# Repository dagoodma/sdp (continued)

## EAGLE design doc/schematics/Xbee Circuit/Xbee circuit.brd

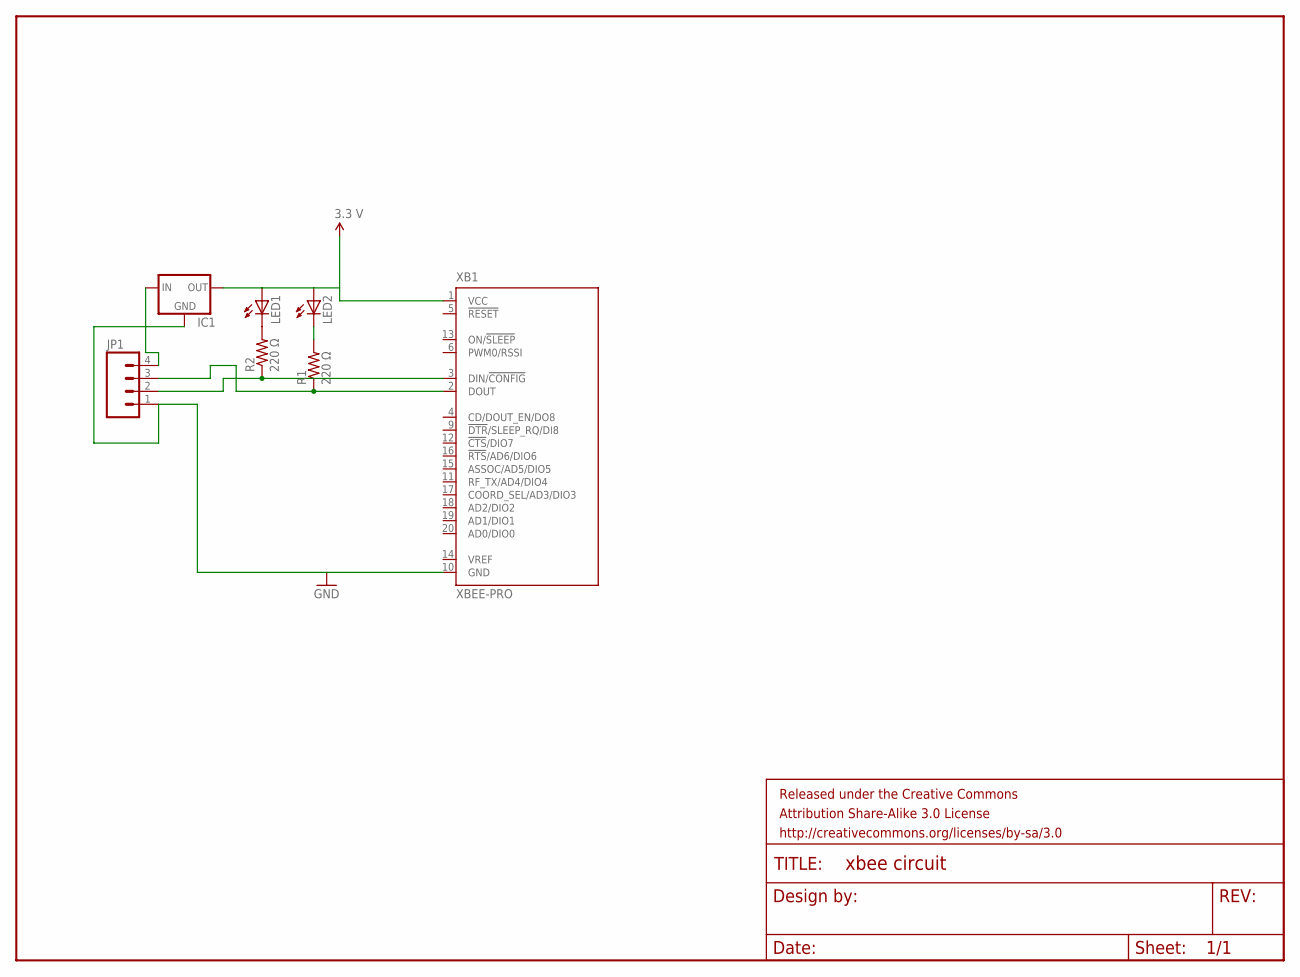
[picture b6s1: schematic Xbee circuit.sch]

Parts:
FRAME1: FRAME-LETTER; CREATIVE_COMMONS
IC1: V_REG_78XXSINK; TO220-IGO
JP1: M04LOCK; 1X04_LOCK
LED1, LED2: LED5MM
R1, R2: 220 Ω; AXIAL-0.4
XB1: XBEE-PRO

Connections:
GND: IC1.GND, JP1.1, XB1.10 (GND)
unnamed: LED2.K (C), R1.P$2 (2)
unnamed: LED1.K (C), R2.P$2 (2)
unnamed: JP1.2, R2.P$1 (1), XB1.3 (DIN/!CONFIG)
unnamed: JP1.3, R1.P$1 (1), XB1.2 (DOUT)
unnamed: IC1.IN, JP1.4
VCC: IC1.OUT, LED1.A, LED2.A, XB1.1 (VCC)

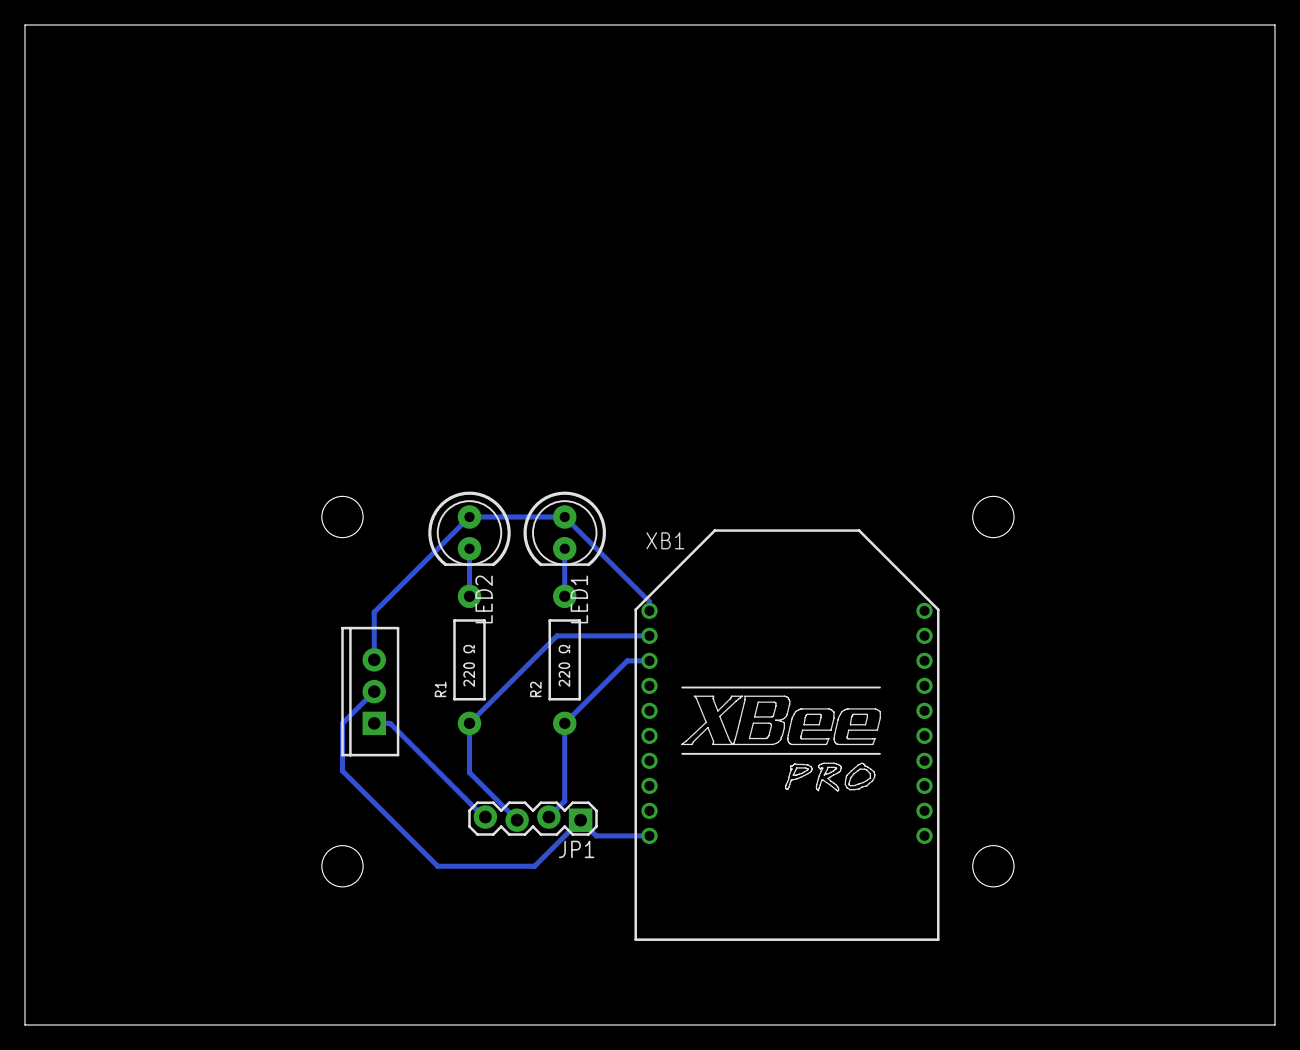
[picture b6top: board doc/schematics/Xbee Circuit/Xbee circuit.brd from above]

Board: 2 copper layers, 100.0 x 80.0 mm, 12 parts (0 on the bottom side), 7 nets.

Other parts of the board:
U$1, U$2, U$3, U$4: STAND-OFF

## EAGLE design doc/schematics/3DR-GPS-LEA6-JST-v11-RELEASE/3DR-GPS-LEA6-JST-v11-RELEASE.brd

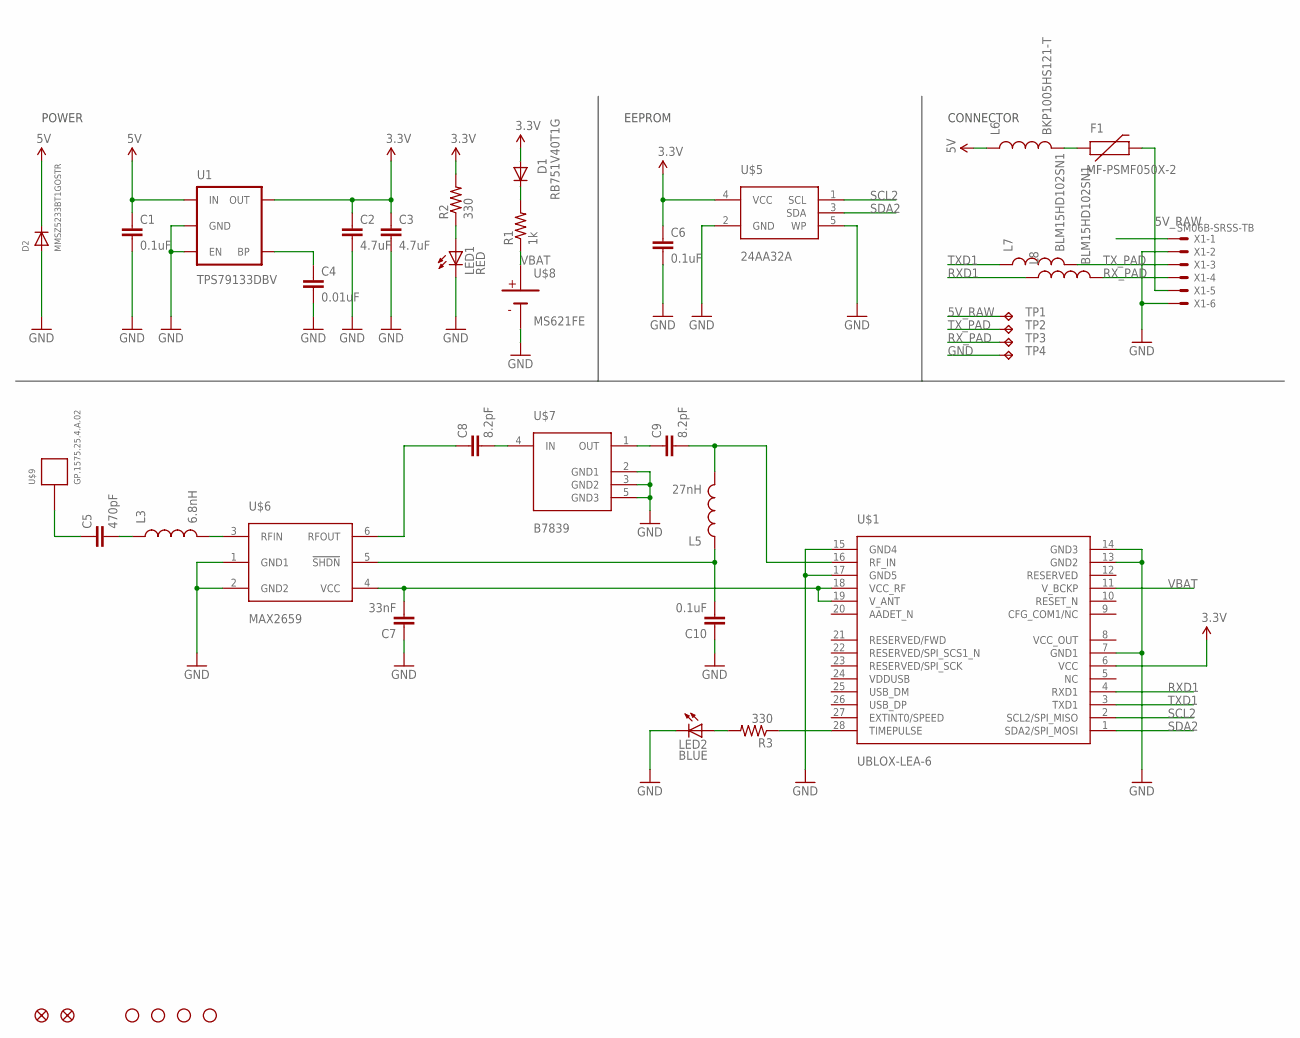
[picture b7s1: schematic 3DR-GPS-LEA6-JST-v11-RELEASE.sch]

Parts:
C1, C6, C10: 0.1uF; 0402-CAP
C2, C3: 4.7uF; 0805
C4: 0.01uF; 0402-CAP
C5: 470pF; 0402-CAP
C7: 33nF; 0402-CAP
C8, C9: 8.2pF; 0402-CAP
D1: RB751V40T1G; SOD-323
D2: MMSZ5233BT1GOSTR; SOD-123
F1: MF-PSMF050X-2; 0805
JP1, JP2: FIDUCIAL1X2; FIDUCIAL-1X2
JP3, JP4, JP5, JP6: STAND-OFF
L3: 6.8nH; C0402
L5: 27nH; C0402
L6: BKP1005HS121-T; 0402-IND
L7, L8: BLM15HD102SN1; 0402-IND
LED1: RED; LED-0603
LED2: BLUE; LED-0603
R1: 1k; 0402-RES
R2, R3: 330; 0402-RES
TP1, TP2, TP3, TP4: TPTP20SQ; TP20SQ
U1: TPS79133DBV; SOT23-5
U$1: UBLOX-LEA-6
U$5: 24AA32A; SOT23-5
U$6: MAX2659; UDFN-6
U$7: B7839; QCS5E
U$8: MS621FE
U$9: GP.1575.25.4.A.02
X1: SM06B-SRSS-TB

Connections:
3.3V: C2.1, C3.1, C6.1, D1.2 (A), R2.2, U1.5 (OUT), U$1.6 (VCC), U$5.4 (VCC)
5V: C1.1, D2.C, L6.1, U1.1 (IN)
5V_RAW: F1.2, TP1.TP, X1.5
GND: C1.2, C2.2, C3.2, C4.2, C6.2, C7.1, C10.1, D2.A, LED1.C, LED2.C, TP4.TP, U1.2 (GND), U1.3 (EN), U$1.7 (GND1), U$1.13 (GND2), U$1.14 (GND3), U$1.15 (GND4), U$1.17 (GND5), U$5.2 (GND), U$5.5 (WP), U$6.1 (GND1), U$6.2 (GND2), U$7.2 (GND1), U$7.3 (GND2), U$7.5 (GND3), U$8.2 (NEG), X1.2, X1.6
unnamed: L3.2, U$6.3 (RFIN)
unnamed: C4.1, U1.4 (BP)
unnamed: C5.2, L3.1
unnamed: C8.2, U$7.4 (IN)
unnamed: R3.1, U$1.28 (TIMEPULSE)
unnamed: C9.1, U$7.1 (OUT)
unnamed: C7.2, U$1.18 (VCC_RF), U$1.19 (V_ANT), U$6.4 (VCC)
unnamed: C8.1, U$6.6 (RFOUT)
unnamed: C10.2, L5.1, U$6.5 (!SHDN)
unnamed: C5.1, U$9.1
unnamed: C9.2, L5.2, U$1.16 (RF_IN)
unnamed: D1.1 (C), R1.2
unnamed: LED1.A, R2.1
unnamed: LED2.A, R3.2
unnamed: F1.1, L6.2
RXD1: L8.1, U$1.4 (RXD1)
RX_PAD: L8.2, TP3.TP, X1.4
SCL2: U$1.2 (SCL2/SPI_MISO), U$5.1 (SCL)
SDA2: U$1.1 (SDA2/SPI_MOSI), U$5.3 (SDA)
TXD1: L7.1, U$1.3 (TXD1)
TX_PAD: L7.2, TP2.TP, X1.3
VBAT: R1.1, U$1.11 (V_BCKP), U$8.1 (POS)

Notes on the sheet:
POWER
EEPROM
CONNECTOR

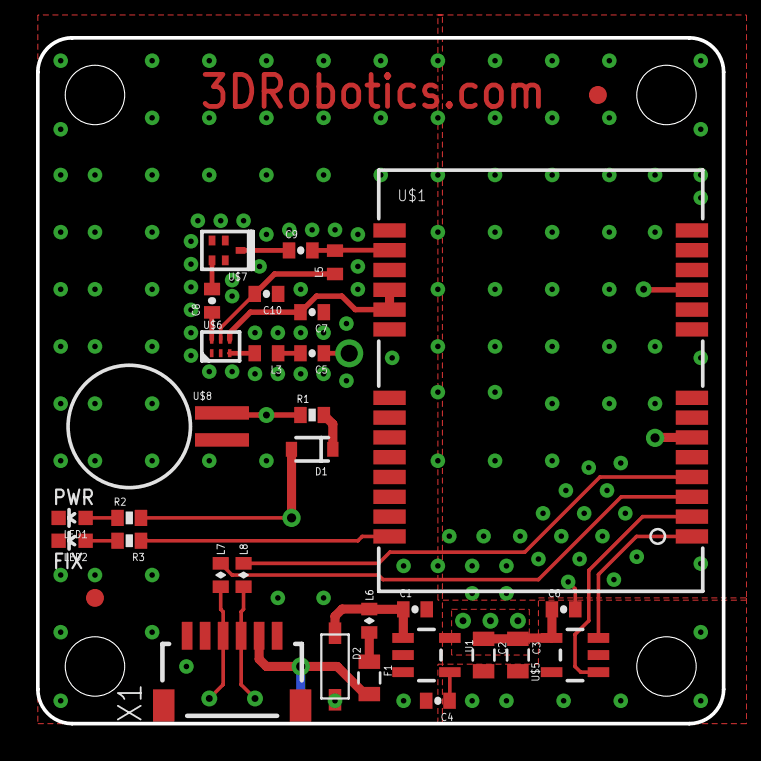
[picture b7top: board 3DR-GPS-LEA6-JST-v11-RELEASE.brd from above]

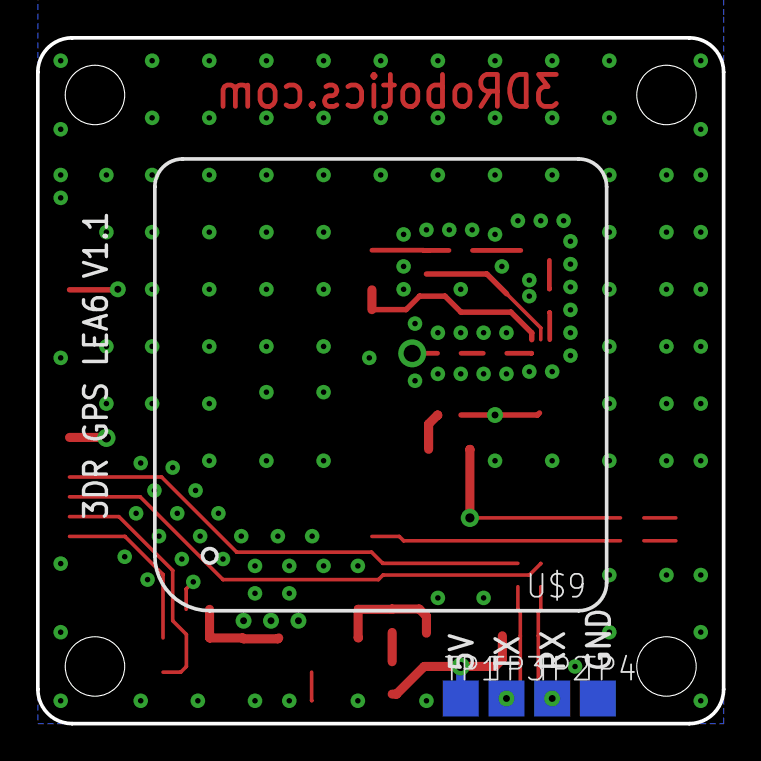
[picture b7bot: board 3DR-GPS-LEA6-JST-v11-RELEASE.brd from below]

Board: 4 copper layers, 38.1 x 38.1 mm, 41 parts (5 on the bottom side), 26 nets.

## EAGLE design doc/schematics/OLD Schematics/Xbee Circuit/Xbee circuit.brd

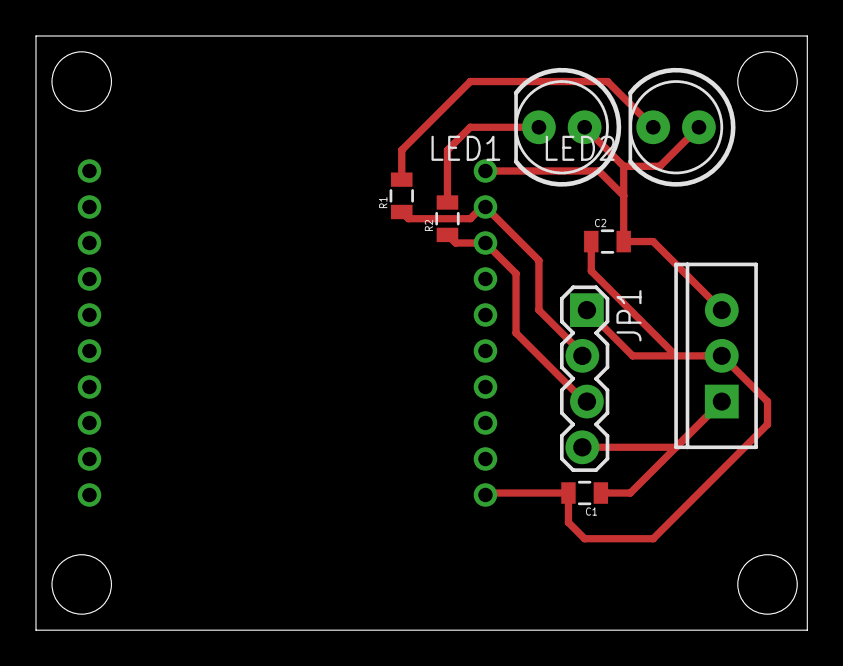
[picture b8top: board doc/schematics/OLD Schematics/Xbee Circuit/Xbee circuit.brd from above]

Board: 2 copper layers, 42.9 x 33.0 mm, 14 parts (1 on the bottom side), 7 nets.

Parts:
C1: 4.7 uF; 0805
C2: 1 uF; 0805
FRAME1: FRAME-LETTER; CREATIVE_COMMONS
IC1: TO220-IGO
JP1: 1X04_LOCK
LED1, LED2: LED5MM
R1, R2: 220 Ω; 0805
U$1, U$2, U$3, U$4: STAND-OFF
XB1: XBEE-PRO

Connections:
GND: C1.2, C2.1, IC1.GND, JP1.1, XB1.10
unnamed: LED2.K, R1.2
unnamed: LED1.K, R2.2
unnamed: JP1.3, R2.1, XB1.3
unnamed: JP1.2, R1.1, XB1.2
unnamed: C1.1, IC1.IN, JP1.4
VCC: C2.2, IC1.OUT, LED1.A, LED2.A, XB1.1

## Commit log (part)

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2012-12-28 Initial commit.
2012-12-28 Added README. Removed braindump.
2012-12-28 Quoted ascii in README.
2012-12-28 Added tool directory.
2012-12-28 Improved github readme.
2013-01-05 Added notes, refs, datasheets, examples folder, images, financial docs, and updated gps model functions.
2013-01-09 Added kresge app, blackwell paper, charter, notes...
2013-01-16 Added presentations.
2013-01-16 Added to Kresge funding proposal.
2013-01-17 Added Background to Kresge Doc
2013-01-17 Objectives section for Funding Proposal
2013-01-17 Added unfinished procedure section.
2013-01-17 Compiled kresge funding doc.
2013-01-17 Added another latex file to gitignore.
2013-01-17 Small change to kresge proposal, reorganized doc folder.
2013-01-17 Finalized kresge proposal cover sheet, budget, and letters of rec.
2013-01-17 Added newest kresge cover sheet.
2013-01-18 Added Kresge funding packet final.
2013-01-19 I2C module Header and C File. Implemented Start, Stop, Send Byte.
2013-01-19 Included the First iteration of the UART code. We still need to test the code and guarantee that it is working properly.
    I also deleted a file that I believe was causing errors. It was 0 bytes, and the folder said that it had been modified, when it had not.
2013-01-19 These are my initial Xbee Files. I believe these are all the files I will need.
    Now that Uart.c is started I can begin implementing the correct functions into the Xbee.c. There will be updated again in the next few days.
2013-01-22 Completed I2C library and Barometer.
2013-01-22 Added local makefile to ignore.
2013-01-23 Updated .gitignore to add temp directory.
2013-01-23 Removed repository files.
2013-01-23 Barometer changes, started accelerometer but not finished.
2013-01-24 Finishing UART and XBee modules.
2013-01-24 Merged Johns Xbee code.
2013-01-25 Reformatted itemized budget. Added thermal MATLAB code, and added data sheets.
2013-01-25 Updated documentation and added doxygen API.
2013-01-25 Added general proposal.
2013-01-29 Finished some of the GPS MATLAB model code. Ready for test.
2013-01-29 Added kml support to GPS model.
2013-01-29 Fixed matlab twos comp conversion issue. Saw correct long lat coordinates.
2013-01-30 Finished 2D scatter plot with stats. Ready for extensive GPS tests.
2013-02-02 Updated comments to code
2013-02-05 Added february newsletter.
2013-02-08 Added GPS code, updated doxygen, added gps data plots, modified Board and Serial modules.
2013-02-10 Updated GPS state machine.
2013-02-10 Thermal module and project added. Ready for MATLAB analysis.
2013-02-10 Merged David and Shahs Barometer code.
2013-02-10 Finished GPS lat,lon,alt code. Still need velocity and error setting.
2013-02-10 Encoders up on new base.
2013-02-10 Non-working encoder code!
2013-02-11 Encoder code that dumps angle value through serial. No running avg. implemented yet.
2013-02-11 Mavlink up and working
2013-02-13 Added serial logging tool and miniterm.
    Next comes py2exe and some fine tuning for serial_logger.
2013-02-13 Small fixes to Xbee Test and #defines
2013-02-14 Added serial logger. Has one error.
    Unexplainable error showing up in data character from serial.read(1):
    Error: Sent byte was not acknowledged
2013-02-14 Finished and merged serial_logger.
2013-02-14 Finished thermal MATLAB code.
2013-02-14 Improved GPS scirpts.
2013-02-14 GPS convergence test. Want mean squared sum now.
2013-02-14 Thermal,baro,and solidworks changes.
2013-02-14 Finished GPS convergence scripts.
2013-02-15 MATLAB code that outputs pixels in the appropriate orientation. Set up for 4Hz.
2013-02-15 Set Xbee Channel into program mode. Tried to make the Send and Recieve dest address working. I was unable to get it to work.
    I also setup XBEE_1 #defines
2013-02-16 Ready to add console window to gui.
2013-02-17 Set up Dest and Source addresses
2013-02-17 Finished gui, but one bug crashes.
2013-02-17 Possibly fixed crashing. Added file menus and removed locks.
2013-02-17 Sonar Compiling
2013-02-23 Finished gui and packed in exe for win.
    Need mac app, and need icon in tkinter.
2013-02-23 New GPS convergence data.
2013-02-23 Finished non-bundles serial_logger, and fixed gps record test to be more robust.
2013-02-23 Fixed gps record test to record timesteps.
2013-02-23 Fixed gps record test time stamps.
2013-02-23 Fixed timestamp recorded gps.
2013-02-23 Fixed timestamps in gps record and improved script.
2013-02-25 xbee Test and Xbee heart beat now working.
2013-02-25 Broken Sonar, about to create a new project.
2013-02-25 Sonar Compiling, and getting proper data. Analog window does not seem to be working.
2013-02-26 Added Mavlink message Start_rescue
2013-02-26 Initial creation of Compass project
2013-02-28 Accelerometer accum and indicator test. Improvements to logger speed.
2013-03-01 Added GPS error correction code to pic, and MATLAB test.
2013-03-07 Message added to Mavlink.c
2013-03-07 Renamed Sonar Project
2013-03-09 Encoders, barometer, Magnetometer, Position module.
2013-03-09 Added Ack, need to transfer over to Compass branch
2013-03-09 Started newletter, added accelerometer into CC.
2013-03-10 Xbee Ack Working
2013-03-10 Added ifdef to compas accelerometer.
2013-03-10 Proper placement of solidworks and schematics
2013-03-10 ACKs now in RUN_SM need to test this on another computer.
2013-03-10 Began work on ACKS
2013-03-10 Navigation library added. Encoder and COMPAS updated with GPS.
2013-03-10 Fixed GPS project, added Navigation, fixed COMPAS.
2013-03-14 Compas compiles with navgiation changes.
2013-03-14 Not compiling, Errors with navigation and Magnetometer functions
2013-03-14 Changed navigation module.
2013-03-14 Fixed navigation NED calculations.
2013-03-15 Edited code for Compas.c
2013-03-15 Added navigation module comment.
2013-03-15 Moved buttons into COMPAS, added defs.
2013-03-15 Checkoff day. Changed height for bridge height.
2013-03-15 Re-enabled Xbee in Compas.
2013-03-23 CLEAN UP SCHEMATICS
2013-03-23 TEST Not working.
2013-03-26 Added new GPS messages to the XML, code still needs to be integrated with them
2013-03-27 GPS error messages integrated into MAVLINK
2013-03-27 Encoder model and ComPAS schematics.
2013-03-27 Added Atlas project and Drive module.
2013-03-27 Wrote updateHeading for Drive module.
    updateHeading function implemented, Controller implemented digitally and Ucmd is utilized in a 1:3 ratio when governing PWM duty cycles for differential motor drive
2013-03-28 Added drive model and march newsletter.
2013-03-28 Fixes to march newsletter.
2013-03-28 Started on boat state machine.
2013-03-29 Updated the updateHeading so that it normalizes the pwm signal so that we may scale it accordingly for any actuator
2013-03-29 Drive module pin changes.
2013-03-29 Created new Barometer Message
    Fixed "North" & "East" to "north" & "east"
2013-03-30 Finished Drive test harness for atlas.
2013-03-30 Updated the DRIVE_TEST harness because initial RC_SERVO pins did not work, I also altered it to work as a state machine to move the motors backwards and forwards. I created my own test harness that t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
2013-03-31 Atlas power management schematic.
2013-03-31 Changed color and took a picture of the render
2013-03-31 Xbee Schematics, created Gerber Files. I do not believe they work.
2013-04-01 Barometer message finished and compiling. Need Shah to help me integrate it into the State Machine.
2013-04-01 Working on atlas drive system.
2013-04-01 Barometer added to compas code.
2013-04-02 Implemented a new test harness which uses an interrupt driven protocol to handle the hand-off between the Micro and Reciever for control. ISR function is included as well as an Override_init which in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
2013-04-02 First type of averaging. Doesn't work very well.
2013-04-04 Atlas and compas changes including GPS integration.
2013-04-05 Implemented updateHeading for rudder control and velocity control
2013-04-05 Schematics: XBEE finished, Compas Started Power supply: looked at.
2013-04-05 Sonar into Matlab.
2013-04-06 Implemented controller for velocity and rudder
2013-04-07 TiltCompass finished and logger started
2013-04-07 Integrated drive code with state machine.
2013-04-07 Finished simple SD logging module. Compiles, ready to test.
2013-04-07 Finished and tested logger module.
2013-04-08 merged rudder init with drive init and changed some test harnesses to test rudder control. It works fine.
2013-04-08 Schematics fixed
2013-04-08 Sonar working, need to integrate mine with Shahs
2013-04-08 Logger, navigation, and drive tested and working.
2013-04-10 New navigation harness almost done.
    Needs override to detect control goes back to the micro controller.
2013-04-11 Added magnetic north offset.
2013-04-11 Revised Test harness for individual actuators and better delay
2013-04-11 More improvements to Navigaton module.
2013-04-12 New schematics
2013-04-12 Fixed GPS course heading, and nav. test ready.
2013-04-12 Finished preliminary Atlas state machine diagrams.
2013-04-12 Merged Darrel drive changes with new navigation.
2013-04-12 Ready to tune drive for navigation test.
2013-04-13 Scaled max motor effort and velocity down.
2013-04-13 Fixed tilt compass offset calculations.
2013-04-15 Changes to drive and navigation from launch 3.
2013-04-15 Xbee updates to tests
2013-04-15 Added waterproof box
2013-04-21 Completed CC box below.
2013-04-21 Cleaned up the XBee circuit
2013-04-22 Nice looking L shape
2013-04-23 Updated L with individual parts
2013-04-27 Mavlink, barometer, and error changes. Ready for John.
2013-04-27 AtLAs SM and Navigation changes.
2013-04-27 Updated Solidworks model from git hub
2013-04-27 * Regenerate from XML * Write code for function headers I put in Mavlink.h (see -Message Status Codes-, I wrote one in Mavlink.c as an example). Also, functions with no ack arguments are assumed ack=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
2013-04-27 Mavlink interface changes.
2013-04-27 Replaced BOOL with bool from stdbool.h, plus Atlas changes.
2013-04-28 Finished AtLAs station machine. Needs debug.
2013-04-28 Cleaned up rudder controller running pivot test and set up for boat launch
2013-04-29 Merged Darrels drive changes and cleaned. Added DBPRINTF.
2013-04-29 Latest Solidwork changes from Drop Box on 4.28.2013
2013-04-29 Successful launch 4.
    Modified Drive module with Darrel's bang-bang changes.
    Switched bang-bang thresholds, added deadband.
    Changed navigation to use percent speed with motors.
2013-05-01 Updates to many modules for AtLAs SM.
2013-05-02 Inital setup of Interface project
2013-05-02 Added a Mavlink command.
2013-05-04 Quick changes to modules. Added old accelerometer schematic.
2013-05-04 Finished ComPAS state machine. New diagrams.
2013-05-04 Finished Interface
2013-05-05 Merged Johns interface in.
2013-05-05 Finished SM and working on GPS fixes.
2013-05-05 Fixed AtLAs errors except ERROR_MESSAGE related
2013-05-07 Atlas and Compas both compiling.
2013-05-11 New interface test harness.
2013-05-11 Fixed Magnetometer negative.
2013-05-12 Merged darrels changes. Added watchdog.
2013-05-12 Debugging ComPAS.
    Initialization succeeded, GPS read failed:
    Initializing magnetomer.
    Initializing encoder.
    Initializing accelerometer.
    Initializing GPS.
    Intializing the GPS on uart 2.
2013-05-13 Updated Interface .h with new buttons and LEDS
2013-05-13 Latest Soldiworks changes
2013-05-14 Still ready for SS test.
2013-05-14 Removed debounce and changed pressed state for new buttons.
2013-05-15 Changes for Compas test.
2013-05-16 Compas nearly works.
2013-05-17 XBee additions of Multicast versus Unicast when programming the mode.
2013-05-17 More changes for bench test.
2013-05-18 Made reset functions static.
2013-05-18 XBee broadcast added.
2013-05-18 Added UART ID parameter to Xbee module.
2013-05-19 Debugging ComPAS interface still.
2013-05-19 Debugging ComPAS modules from johns comp.
2013-05-19 Debugging ComPAS, AtLAs, and Watchdog.
2013-05-19 Debugging ComPAS and AtLAs together.
2013-05-21 Atlas ready without GPS. Compas reset light feature.
2013-05-21 Compas and AtLAs are working without GPS.
2013-05-22 Debug ready for outside. Debugging Drive.
2013-05-22 Ready for Wednesday launch.
2013-05-24 Launch before checkoff. Tuned controls.
